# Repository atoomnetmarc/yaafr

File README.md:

# What are this?

This is Yaafr, Yet Another AVR Fusebit Rescuer. It is large because of all the ZIF-sockets and does not even feature any mounting holes. It also has two IDC headers for expanding to programming clips or other adapters to rescue non-dip AVR microcontrollers.

It is be able to restore wrongly fused or locked AVR microcontrollers that support high voltage parallel (HVPP) programming or high voltage serial programming (HVSP).

This circuit has been inspired by these projects:

[RescueAVR](https://github.com/felias-fogg/RescueAVR) by Bernhard.\
[AVR Fuse Rescue Shield for Arduino Uno](https://github.com/4x1md/avr_frs_shield) by Dmitry Melnichansky.\
[Arduino-based AVR High Voltage Programmer](https://mightyohm.com/blog/2008/09/arduino-based-avr-high-voltage-programmer/) by Jeff Keyzer.\
[Atmega Fusebit Doctor](https://web.archive.org/web/20180225102717/http://mdiy.pl/atmega-fusebit-doctor-hvpp/?lang=en) by Paweł Kisielewski.

Firmware update 2.11 from the Atmega Fusebit Doctor for the atmega328p has been tested and is working. The [original site](https://files.elektroda.pl/437268,atmega-hvpp-fusebit-doctor_update11.html) does not exist anymore, but [SukkoPera](https://github.com/SukkoPera) has been so kind to archive the remains: https://github.com/SukkoPera/avr-fusebit-doctor/

Firmware from RescueAVR in FBD_MODE works also, but may not contain support for all the chips (such as the AT90S1200).

# Status

This project is working for me, I can rescue all my locked AVRs. See below for what I have tested and validated to be working.

While the schematic was carefully made, the PCB has not been fully tested yet.

I added the possibility to switch on and off AGND and AVCC because in many datasheets in one instance they must be connected and in the next they must not, however leaving the switches always on connected when it does not need to be then the rescues seem to work just fine.

# Checklists

## Functionality

| Thing                                         | Tested and working?       |
| --                                            | --                        |
| 40-pin DIP style A                            | :ballot_box_with_check:   |
| 40-pin DIP style B                            | :ballot_box_with_check:   |
| 28-pin DIP style A                            | :ballot_box_with_check:   |
| 20-pin DIP style A                            | :ballot_box_with_check:   |
| 20-pin DIP style B                            | :ballot_box_with_check:   |
| 14-pin DIP style A                            | :ballot_box_with_check:   |
| 8-pin DIP style A                             | :ballot_box_with_check:   |
| AVR Atmega fusebit doctor firmware 2.11       | :ballot_box_with_check:   |
| RescueAVR firmware                            | :ballot_box_with_check:   |
| Serial connection                             | :ballot_box_with_check:   |
| Fusebit doctor compatible expansion header    | :ballot_box_with_check:   |
| HVPP expansion header                         | :black_square_button:     |
| HVSP expansion header                         | :black_square_button:     |

## 40-pin DIP style A (AT90S8535)

| Model         | Signature         | Working                   |
| --            | --                | --                        |
| AT90S8535     | 0x1E 0x93 0x03    | :ballot_box_with_check:   |
| ATmega8535    | 0x1E 0x93 0x08    | :ballot_box_with_check:   |
| ATmega163     | 0x1E 0x94 0x02    | :ballot_box_with_check:   |
| ATmega323     | 0x1E 0x95 0x01    | :ballot_box_with_check:   |
| ATmega16A     | 0x1E 0x94 0x03    | :ballot_box_with_check:   |
| ATmega32A     | 0x1E 0x95 0x02    | :ballot_box_with_check:   |
| ATmega324A    | 0x1E 0x95 0x15    | :ballot_box_with_check:   |
| ATmega644PA   | 0x1E 0x96 0x0A    | :ballot_box_with_check:   |
| ATmega1284P   | 0x1E 0x97 0x05    | :ballot_box_with_check:   |

## 40-pin DIP style B (AT90S8515)

| Model         | Signature         | Working                   |
| --            | --                | --                        |
| AT90S4414     | 0x1E 0x92 0x01    | :ballot_box_with_check:   |
| AT90S8515     | 0x1E 0x93 0x01    | :ballot_box_with_check:   |
| ATmega8515    | 0x1E 0x93 0x06    | :ballot_box_with_check:   |
| ATmega161     | 0x1E 0x94 0x01    | :ballot_box_with_check:   |
| ATmega162     | 0x1E 0x94 0x04    | :ballot_box_with_check:   |

## 28-pin DIP style A (AT90S2333)

| Model     | Signature         | Working                   |
| --        | --                | --                        |
| AT90S2333 | 0x1E 0x91 0x05    | :ballot_box_with_check:   |
| AT90S4433 | 0x1E 0x92 0x03    | :ballot_box_with_check:   |
| ATmega8   | 0x1E 0x93 0x07    | :ballot_box_with_check:   |
| ATmega48  | 0x1E 0x92 0x05    | :ballot_box_with_check:   |
| ATmega88  | 0x1E 0x93 0x0A    | :ballot_box_with_check:   |
| ATmega168 | 0x1E 0x94 0x06    | :ballot_box_with_check:   |
| ATmega328 | 0x1E 0x95 0x14    | :ballot_box_with_check:   |
| ATtiny48  | 0x1E 0x92 0x09    | :ballot_box_with_check:   |
| ATtiny88  | 0x1E 0x93 0x11    | :ballot_box_with_check:   |

Adapter for TQFP32: https://github.com/atoomnetmarc/Fusebit-Doctor-TQFP32-adapter

## 20-pin DIP style A (AT90S1200)

| Model         | Signature         | Working                   |
| --            | --                | --                        |
| AT90S1200     | 0x1E 0x90 0x01    | :ballot_box_with_check:   |
| AT90S2313     | 0x1E 0x91 0x01    | :ballot_box_with_check:   |
| ATtiny2313    | 0x1E 0x91 0x0A    | :ballot_box_with_check:   |
| ATtiny2313A   | 0x1E 0x91 0x0A    | :ballot_box_with_check:   |
| ATtiny4313    | 0x1E 0x92 0x0D    | :ballot_box_with_check:   |

## 20-pin DIP style B (ATtiny26)

| Model         | Signature         | Working                   |
| --            | --                | --                        |
| ATtiny26      | 0x1E 0x91 0x09    | :ballot_box_with_check:   |
| ATtiny261A    | 0x1E 0x91 0x0C    | :ballot_box_with_check:   |
| ATtiny461     | 0x1E 0x92 0x08    | :ballot_box_with_check:   |
| ATtiny461A    | 0x1E 0x92 0x08    | :ballot_box_with_check:   |
| ATtiny861A    | 0x1E 0x93 0x0D    | :ballot_box_with_check:   |

## 14-pin DIP style A (ATtiny24)

| Model     | Signature         | Working                   |
| --        | --                | --                        |
| ATtiny24  | 0x1E 0x91 0x0B    | :ballot_box_with_check:   |

## 8-pin DIP style A (AT90S2323)

| Model     | Signature         | Working                   |
| --        | --                | --                        |
| AT90S2323 | 0x1E 0x91 0x02    | :ballot_box_with_check:   |
| AT90S2343 | 0x1E 0x91 0x03    | :ballot_box_with_check:   |
| ATtiny12  | 0x1E 0x90 0x05    | :ballot_box_with_check:   |
| ATtiny15  | 0x1E 0x90 0x06    | :ballot_box_with_check:   |
| ATtiny13  | 0x1E 0x90 0x07    | :ballot_box_with_check:   |
| ATtiny25  | 0x1E 0x91 0x08    | :ballot_box_with_check:   |
| ATtiny45  | 0x1E 0x92 0x06    | :ballot_box_with_check:   |
| ATtiny85  | 0x1E 0x93 0x0B    | :ballot_box_with_check:   |

# Errata

## PCB V1.1

- No known erratum, however this pcb version has not been made yet.

## PCB V1.0

- 10.16mm wide 28-pin ZIF socket X3 seems to be unobtanium. Changed for 7.62mm wide 'narrow' 28-pin zif socket in V1.1 pcb.

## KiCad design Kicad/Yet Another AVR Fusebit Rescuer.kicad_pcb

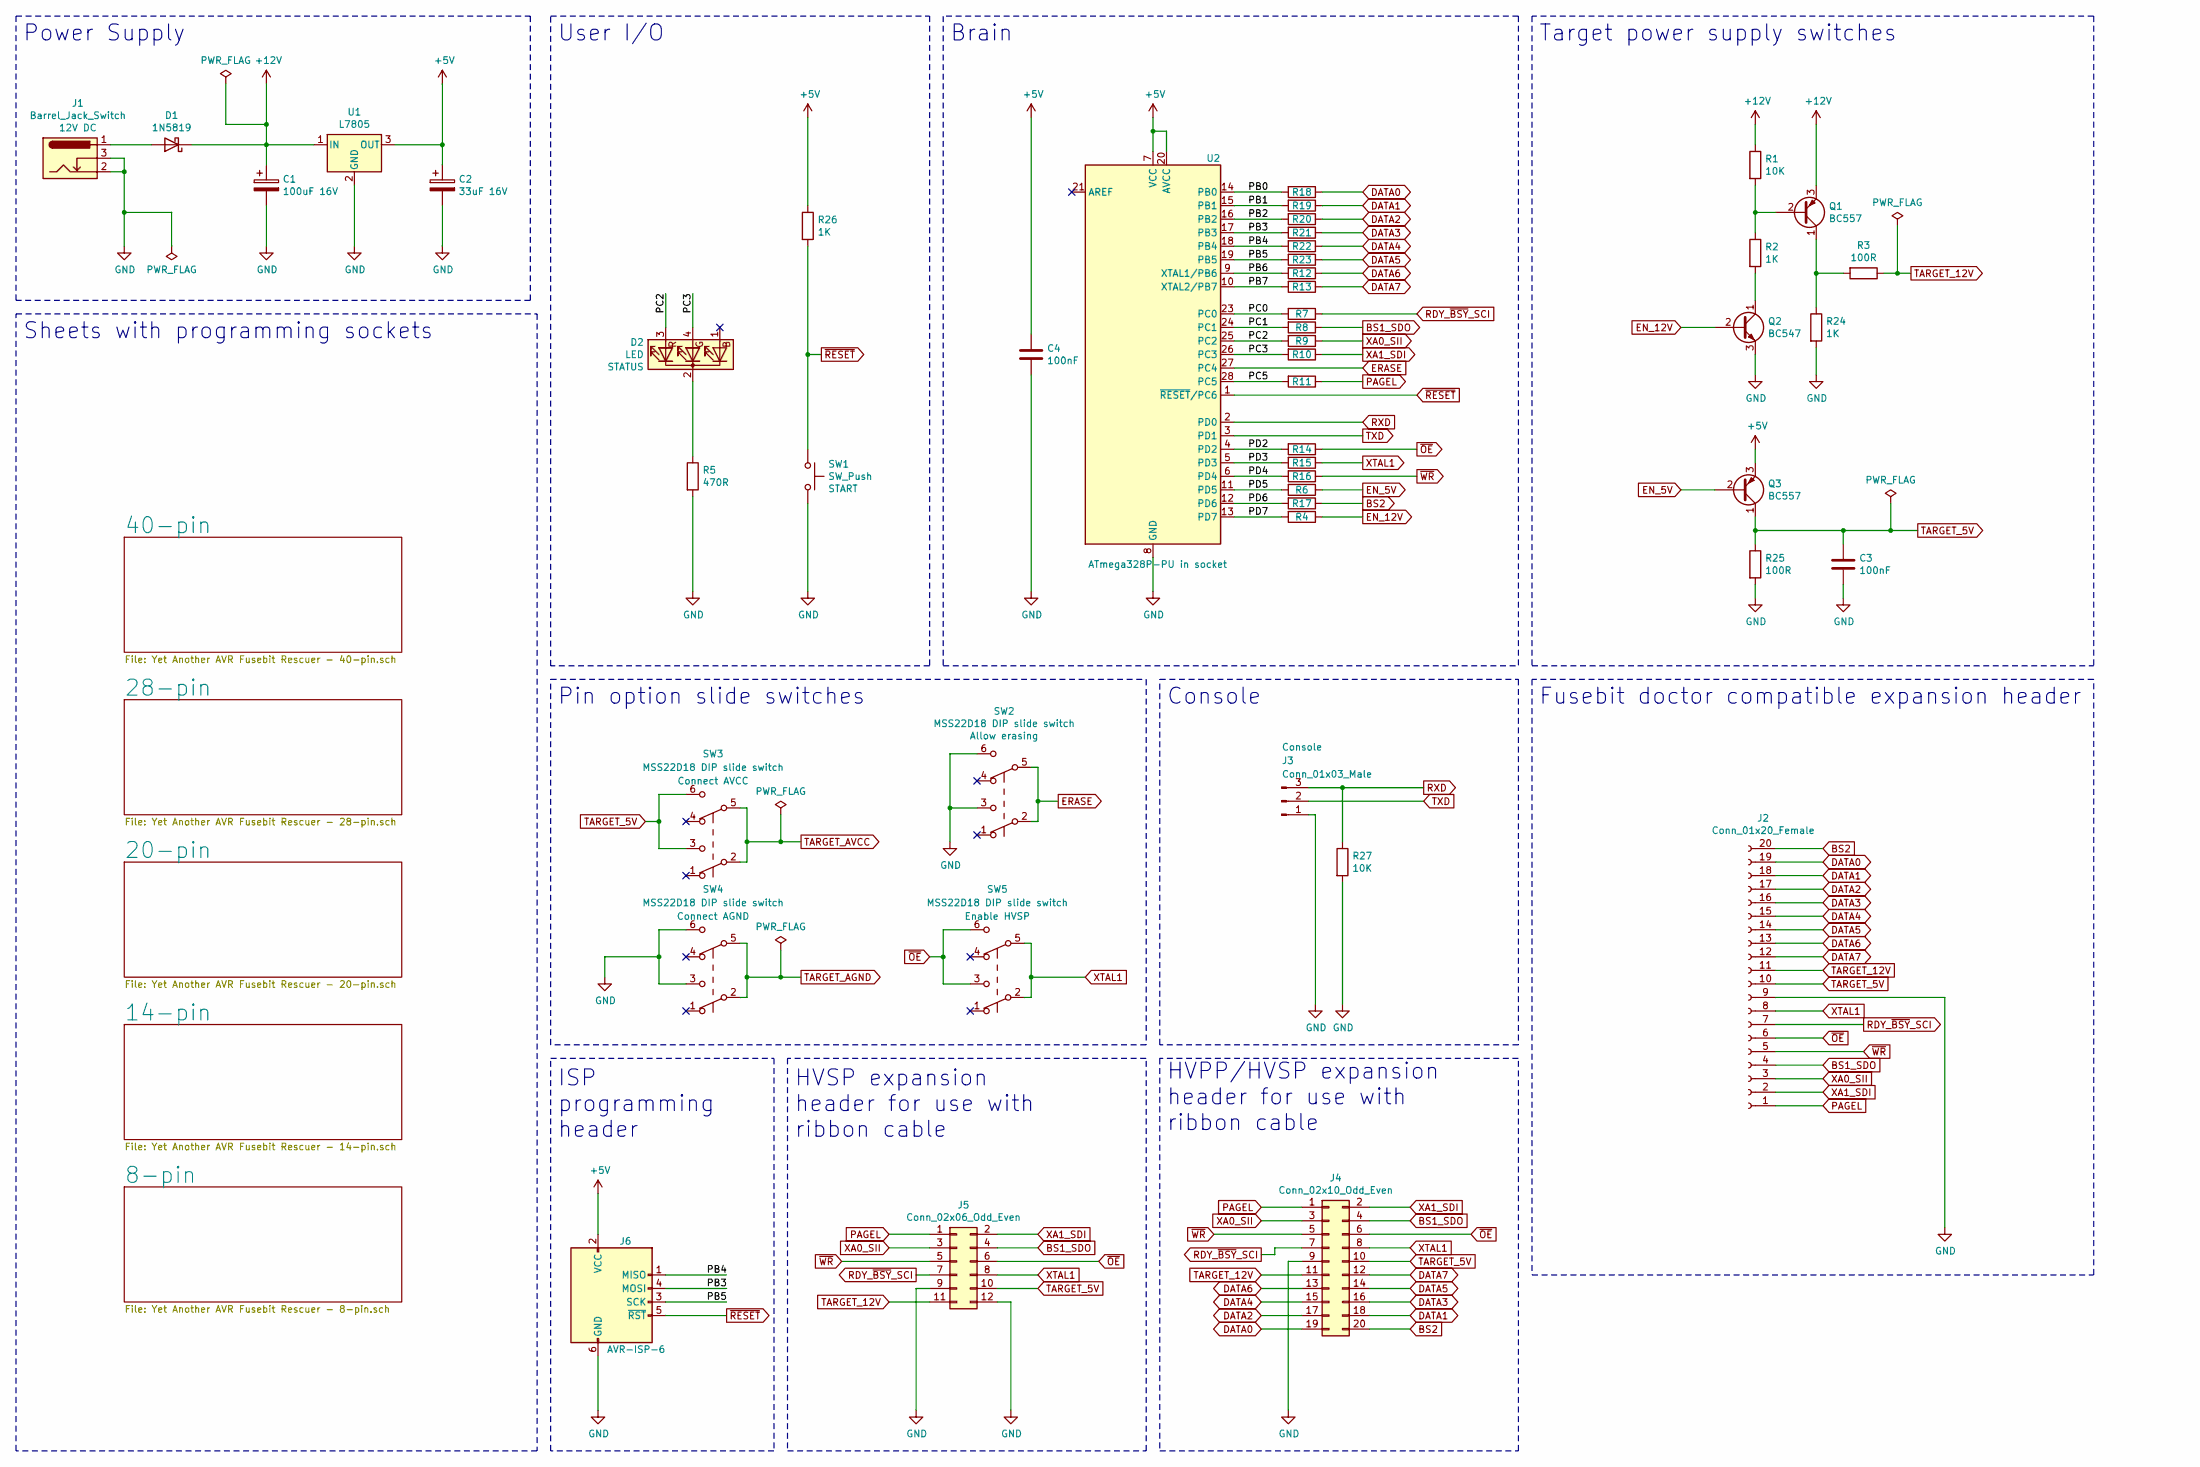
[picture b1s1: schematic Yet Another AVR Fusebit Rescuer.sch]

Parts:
C1: 100uF 16V; CP_Radial_D6.3mm_P2.50mm
C2: 33uF 16V; CP_Radial_D6.3mm_P2.50mm
C3, C4: 100nF; C_Disc_D5.1mm_W3.2mm_P5.00mm
D1: 1N5819; D_DO-15_P12.70mm_Horizontal
D2: LED; LED_D5.0mm-4_RGB
J1: Barrel_Jack_Switch; BarrelJack_Horizontal
J2: Conn_01x20_Female; PinSocket_1x20_P2.54mm_Vertical
J3: Conn_01x03_Male; PinHeader_1x03_P2.54mm_Horizontal
J4: Conn_02x10_Odd_Even; IDC-Header_2x10_P2.54mm_Vertical
J5: Conn_02x06_Odd_Even; IDC-Header_2x06_P2.54mm_Vertical
J6: AVR-ISP-6; IDC-Header_2x03_P2.54mm_Vertical
Q1, Q3: BC557; TO-92_Wide
Q2: BC547; TO-92_Wide
R1, R27: 10K; R_Axial_DIN0207_L6.3mm_D2.5mm_P10.16mm_Horizontal
R2, R4, R6, R7, R8, R9, R10, R11, R12, R13, R14, R15, R16, R17, R18, R19, R20, R21, R22, R23, R24, R26: 1K; R_Axial_DIN0207_L6.3mm_D2.5mm_P10.16mm_Horizontal
R3, R25: 100R; R_Axial_DIN0207_L6.3mm_D2.5mm_P10.16mm_Horizontal
R5: 470R; R_Axial_DIN0207_L6.3mm_D2.5mm_P10.16mm_Horizontal
SW1: SW_Push; SW_PUSH_6mm
SW2, SW3, SW4, SW5: MSS22D18 DIP slide switch; SW_CuK_JS202011CQN_DPDT_Straight
U1: L7805; TO-220-3_Horizontal_TabDown
U2: ATmega328P-PU in socket; DIP-28_W7.62mm

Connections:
+5V: C2.1, C4.1, J6.2 (VCC), Q3.3 (E), R26.1, U1.3 (OUT), U2.7 (VCC), U2.20 (AVCC)
+12V: C1.1, D1.1 (K), Q1.3 (E), R1.1, U1.1 (IN)
/PB0: R18.2, U2.14 (PB0)
/PB1: R19.2, U2.15 (PB1)
/PB2: R20.2, U2.16 (PB2)
/PB3: J6.4 (MOSI), R21.2, U2.17 (PB3)
/PB4: J6.1 (MISO), R22.2, U2.18 (PB4)
/PB5: J6.3 (SCK), R23.2, U2.19 (PB5)
/PB6: R12.2, U2.9 (XTAL1/PB6)
/PB7: R13.2, U2.10 (XTAL2/PB7)
/PC0: R7.2, U2.23 (PC0)
/PC1: R8.2, U2.24 (PC1)
/PC2: D2.3 (RA), R9.2, U2.25 (PC2)
/PC3: D2.4 (GA), R10.2, U2.26 (PC3)
/PC5: R11.2, U2.28 (PC5)
/PD2: R14.2, U2.4 (PD2)
/PD3: R15.2, U2.5 (PD3)
/PD4: R16.2, U2.6 (PD4)
/PD5: R6.2, U2.11 (PD5)
/PD6: R17.2, U2.12 (PD6)
/PD7: R4.2, U2.13 (PD7)
BS1_SDO: J2.4, J4.4, J5.4, R8.1; also elsewhere on the board
BS2: J2.20, J4.20, R17.1; also elsewhere on the board
DATA0: J2.19, J4.19, R18.1; also elsewhere on the board
DATA1: J2.18, J4.18, R19.1; also elsewhere on the board
DATA2: J2.17, J4.17, R20.1; also elsewhere on the board
DATA3: J2.16, J4.16, R21.1; also elsewhere on the board
DATA4: J2.15, J4.15, R22.1; also elsewhere on the board
DATA5: J2.14, J4.14, R23.1; also elsewhere on the board
DATA6: J2.13, J4.13, R12.1; also elsewhere on the board
DATA7: J2.12, J4.12, R13.1; also elsewhere on the board
EN_5V: Q3.2 (B), R6.1
EN_12V: Q2.2 (B), R4.1
ERASE: SW2.2 (B), SW2.5 (B), U2.27 (PC4)
GND: C1.2, C2.2, C3.2, C4.2, J1.2, J1.3, J2.9, J3.1, J4.9, J5.9, J5.12, J6.6 (GND), Q2.3 (E), R5.2, R24.2, R25.2, R27.2, SW1.2, SW2.3 (C), SW2.6 (C), SW4.3 (C), SW4.6 (C), U1.2 (GND), U2.8 (GND), U2.22 (GND); also elsewhere on the board
unnamed: D1.2 (A), J1.1
unnamed: D2.2 (K), R5.1
unnamed: Q1.1 (C), R3.2, R24.1
unnamed: Q1.2 (B), R1.2, R2.1
unnamed: Q2.1 (C), R2.2
PAGEL: J2.1, J4.1, J5.1, R11.1; also elsewhere on the board
RDY_~BSY~_SCI: J2.7, J4.7, J5.7, R7.1; also elsewhere on the board
RXD: J3.3, R27.1, U2.2 (PD0)
TARGET_5V: C3.1, J2.10, J4.10, J5.10, Q3.1 (C), R25.1, SW3.3 (C), SW3.6 (C); also elsewhere on the board
TARGET_12V: J2.11, J4.11, J5.11, R3.1; also elsewhere on the board
TARGET_AGND: SW4.2 (B), SW4.5 (B); also elsewhere on the board
TARGET_AVCC: SW3.2 (B), SW3.5 (B); also elsewhere on the board
TXD: J3.2, U2.3 (PD1)
XA0_SII: J2.3, J4.3, J5.3, R9.1; also elsewhere on the board
XA1_SDI: J2.2, J4.2, J5.2, R10.1; also elsewhere on the board
XTAL1: J2.8, J4.8, J5.8, R15.1, SW5.2 (B), SW5.5 (B); also elsewhere on the board
~OE: J2.6, J4.6, J5.6, R14.1, SW5.3 (C), SW5.6 (C); also elsewhere on the board
~RESET: J6.5 (~RST), R26.2, SW1.1, U2.1 (~RESET~/PC6)
~WR: J2.5, J4.5, J5.5, R16.1; also elsewhere on the board

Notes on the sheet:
Power Supply
Target power supply switches
Fusebit doctor compatible expansion header
User I/O
Console
Brain
Pin option slide switches
HVPP/HVSP expansion header for use with ribbon cable
HVSP expansion header for use with ribbon cable
ISP programming header
Sheets with programming sockets

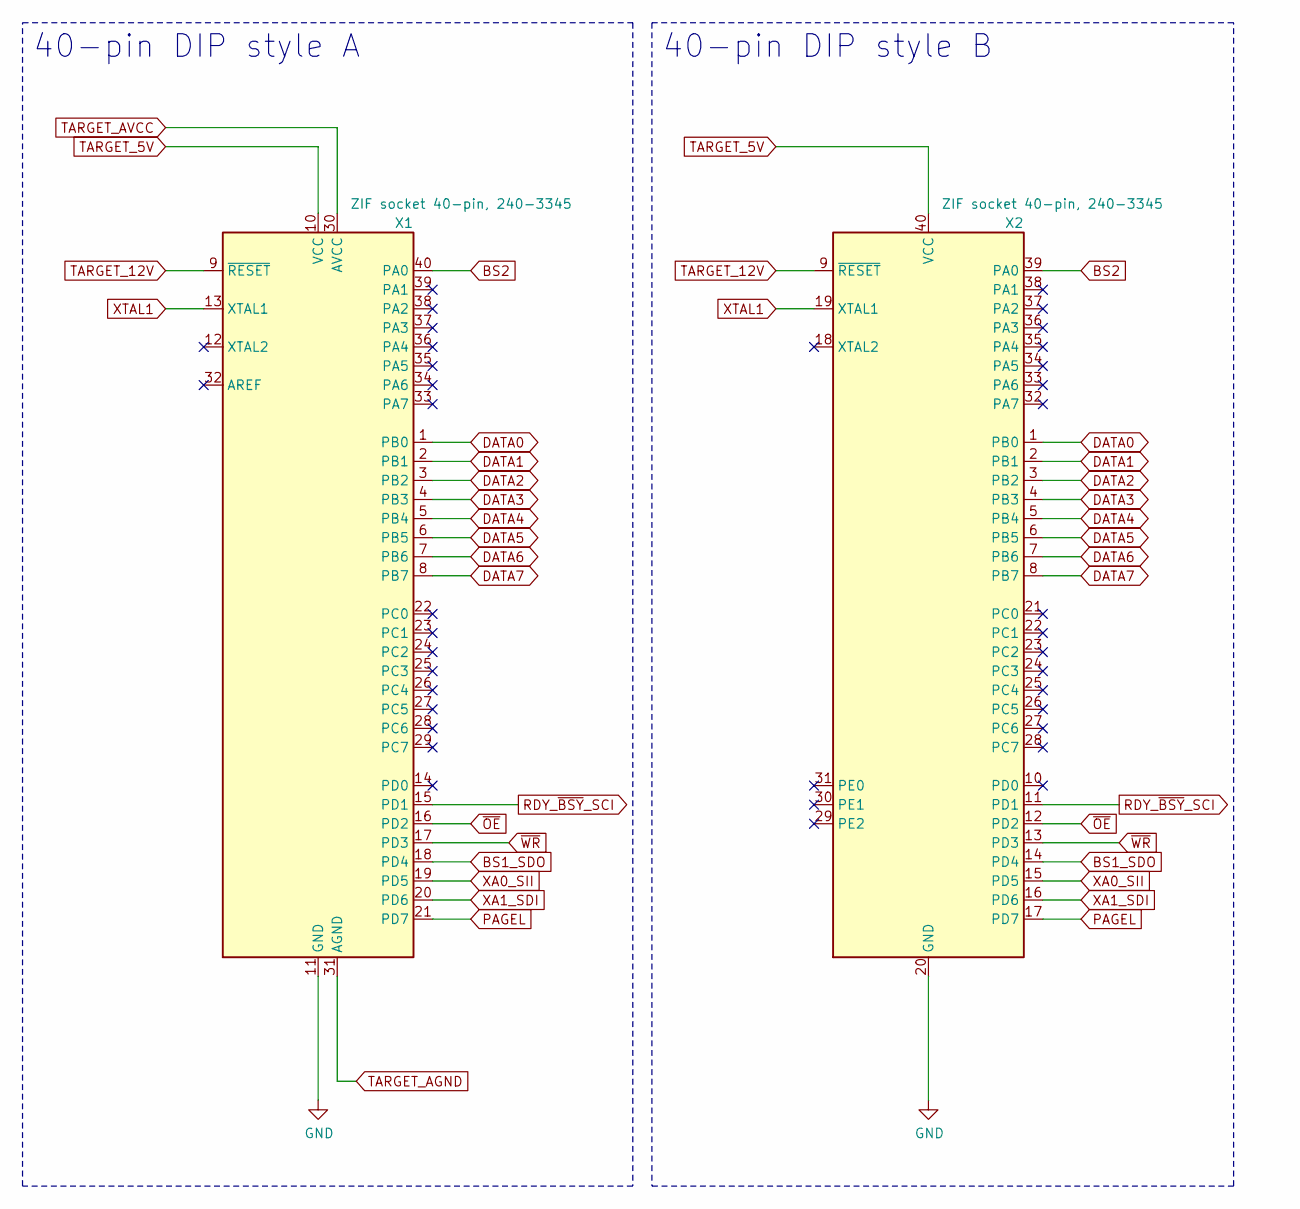
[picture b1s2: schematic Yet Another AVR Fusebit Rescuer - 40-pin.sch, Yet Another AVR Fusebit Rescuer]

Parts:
X1, X2: ZIF socket 40-pin, 240-3345; DIP_Socket-40_W11.9_W12.7_W15.24_W17.78_W18.5_3M_240-1280-0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

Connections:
BS1_SDO: X1.18 (PD4), X2.14 (PD4); also elsewhere on the board
BS2: X1.40 (PA0), X2.39 (PA0); also elsewhere on the board
DATA0: X1.1 (PB0), X2.1 (PB0); also elsewhere on the board
DATA1: X1.2 (PB1), X2.2 (PB1); also elsewhere on the board
DATA2: X1.3 (PB2), X2.3 (PB2); also elsewhere on the board
DATA3: X1.4 (PB3), X2.4 (PB3); also elsewhere on the board
DATA4: X1.5 (PB4), X2.5 (PB4); also elsewhere on the board
DATA5: X1.6 (PB5), X2.6 (PB5); also elsewhere on the board
DATA6: X1.7 (PB6), X2.7 (PB6); also elsewhere on the board
DATA7: X1.8 (PB7), X2.8 (PB7); also elsewhere on the board
GND: X1.11 (GND), X2.20 (GND); also elsewhere on the board
PAGEL: X1.21 (PD7), X2.17 (PD7); also elsewhere on the board
RDY_~BSY~_SCI: X1.15 (PD1), X2.11 (PD1); also elsewhere on the board
TARGET_5V: X1.10 (VCC), X2.40 (VCC); also elsewhere on the board
TARGET_12V: X1.9 (~RESET), X2.9 (~RESET); also elsewhere on the board
TARGET_AGND: X1.31 (AGND); also elsewhere on the board
TARGET_AVCC: X1.30 (AVCC); also elsewhere on the board
XA0_SII: X1.19 (PD5), X2.15 (PD5); also elsewhere on the board
XA1_SDI: X1.20 (PD6), X2.16 (PD6); also elsewhere on the board
XTAL1: X1.13 (XTAL1), X2.19 (XTAL1); also elsewhere on the board
~OE: X1.16 (PD2), X2.12 (PD2); also elsewhere on the board
~WR: X1.17 (PD3), X2.13 (PD3); also elsewhere on the board

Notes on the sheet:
40-pin DIP style A
40-pin DIP style B

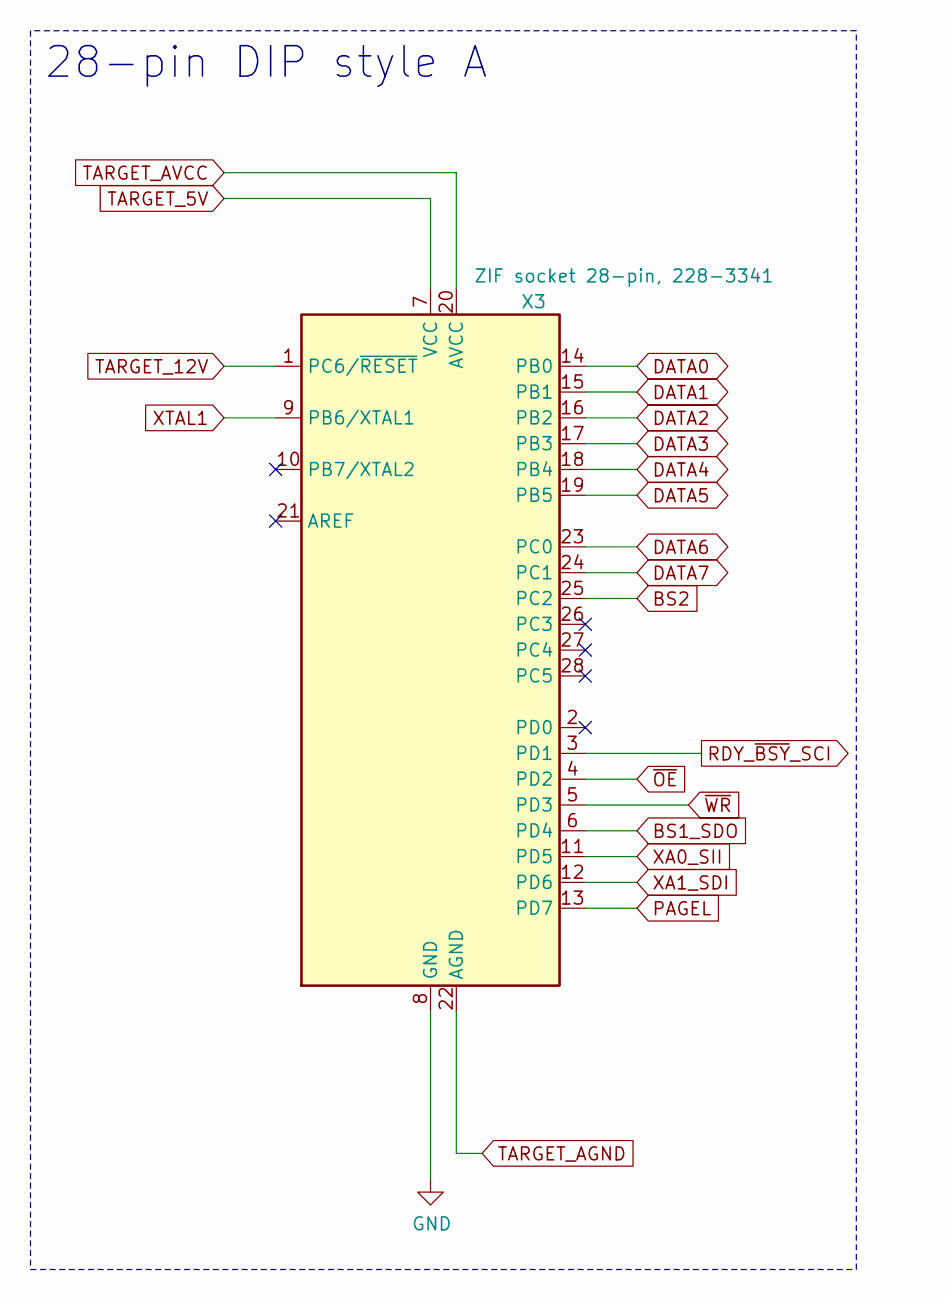
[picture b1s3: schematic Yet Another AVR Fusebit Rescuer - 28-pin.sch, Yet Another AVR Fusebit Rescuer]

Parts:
X3: ZIF socket 28-pin, 228-3341; DIP_Socket-28_228-3341

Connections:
BS1_SDO: X3.6 (PD4); also elsewhere on the board
BS2: X3.25 (PC2); also elsewhere on the board
DATA0: X3.14 (PB0); also elsewhere on the board
DATA1: X3.15 (PB1); also elsewhere on the board
DATA2: X3.16 (PB2); also elsewhere on the board
DATA3: X3.17 (PB3); also elsewhere on the board
DATA4: X3.18 (PB4); also elsewhere on the board
DATA5: X3.19 (PB5); also elsewhere on the board
DATA6: X3.23 (PC0); also elsewhere on the board
DATA7: X3.24 (PC1); also elsewhere on the board
GND: X3.8 (GND); also elsewhere on the board
PAGEL: X3.13 (PD7); also elsewhere on the board
RDY_~BSY~_SCI: X3.3 (PD1); also elsewhere on the board
TARGET_5V: X3.7 (VCC); also elsewhere on the board
TARGET_12V: X3.1 (PC6/~RESET); also elsewhere on the board
TARGET_AGND: X3.22 (AGND); also elsewhere on the board
TARGET_AVCC: X3.20 (AVCC); also elsewhere on the board
XA0_SII: X3.11 (PD5); also elsewhere on the board
XA1_SDI: X3.12 (PD6); also elsewhere on the board
XTAL1: X3.9 (PB6/XTAL1); also elsewhere on the board
~OE: X3.4 (PD2); also elsewhere on the board
~WR: X3.5 (PD3); also elsewhere on the board

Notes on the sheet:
28-pin DIP style A

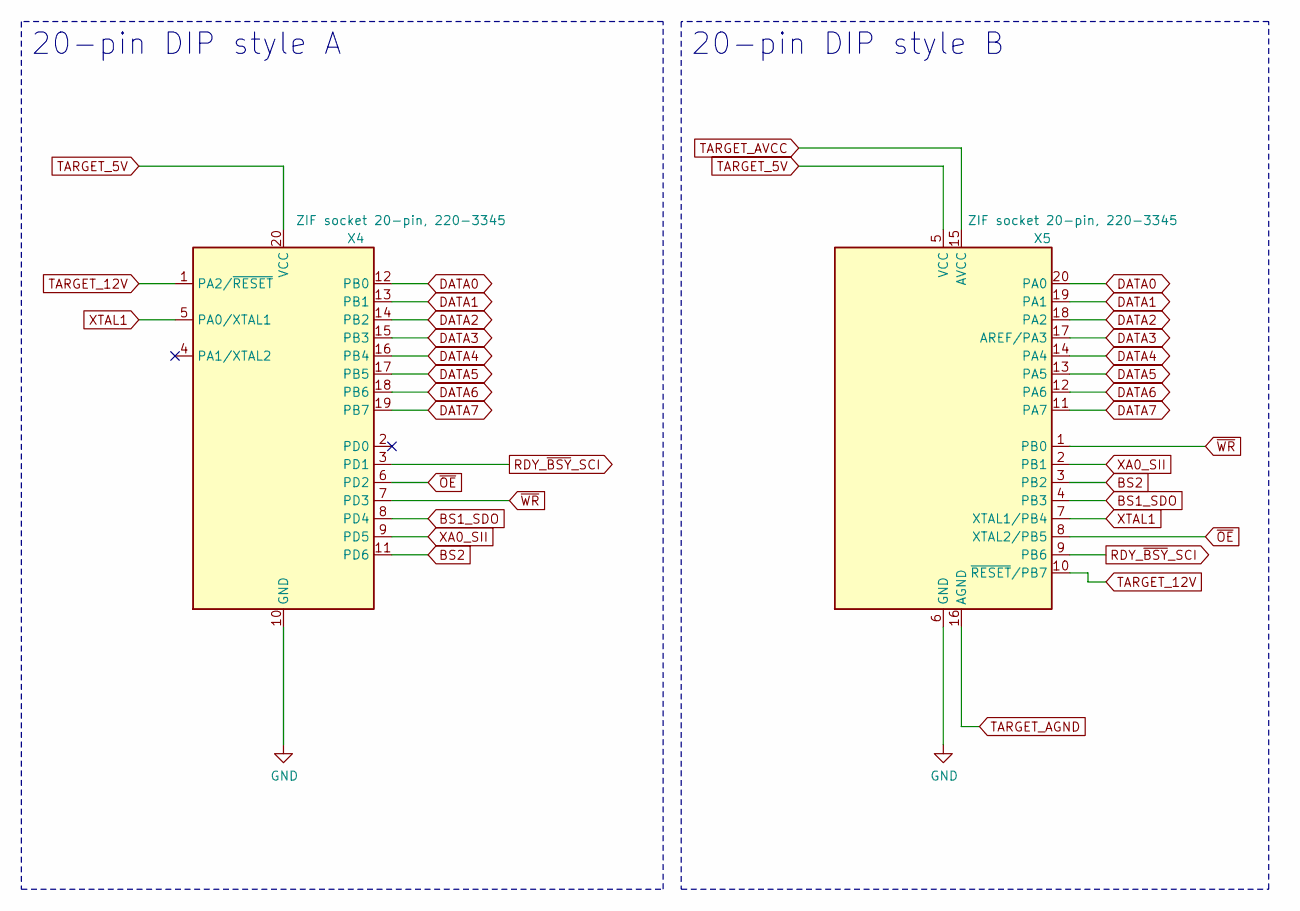
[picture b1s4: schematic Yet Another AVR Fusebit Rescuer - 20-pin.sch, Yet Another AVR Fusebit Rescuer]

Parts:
X4, X5: ZIF socket 20-pin, 220-3345; DIP_Socket-20_W4.3_W5.08_W7.62_W10.16_W10.9_3M_220-3342-00-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

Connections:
BS1_SDO: X4.8 (PD4), X5.4 (PB3); also elsewhere on the board
BS2: X4.11 (PD6), X5.3 (PB2); also elsewhere on the board
DATA0: X4.12 (PB0), X5.20 (PA0); also elsewhere on the board
DATA1: X4.13 (PB1), X5.19 (PA1); also elsewhere on the board
DATA2: X4.14 (PB2), X5.18 (PA2); also elsewhere on the board
DATA3: X4.15 (PB3), X5.17 (AREF/PA3); also elsewhere on the board
DATA4: X4.16 (PB4), X5.14 (PA4); also elsewhere on the board
DATA5: X4.17 (PB5), X5.13 (PA5); also elsewhere on the board
DATA6: X4.18 (PB6), X5.12 (PA6); also elsewhere on the board
DATA7: X4.19 (PB7), X5.11 (PA7); also elsewhere on the board
GND: X4.10 (GND), X5.6 (GND); also elsewhere on the board
RDY_~BSY~_SCI: X4.3 (PD1), X5.9 (PB6); also elsewhere on the board
TARGET_5V: X4.20 (VCC), X5.5 (VCC); also elsewhere on the board
TARGET_12V: X4.1 (PA2/~RESET), X5.10 (~RESET~/PB7); also elsewhere on the board
TARGET_AGND: X5.16 (AGND); also elsewhere on the board
TARGET_AVCC: X5.15 (AVCC); also elsewhere on the board
XA0_SII: X4.9 (PD5), X5.2 (PB1); also elsewhere on the board
XTAL1: X4.5 (PA0/XTAL1), X5.7 (XTAL1/PB4); also elsewhere on the board
~OE: X4.6 (PD2), X5.8 (XTAL2/PB5); also elsewhere on the board
~WR: X4.7 (PD3), X5.1 (PB0); also elsewhere on the board

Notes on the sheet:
20-pin DIP style A
20-pin DIP style B

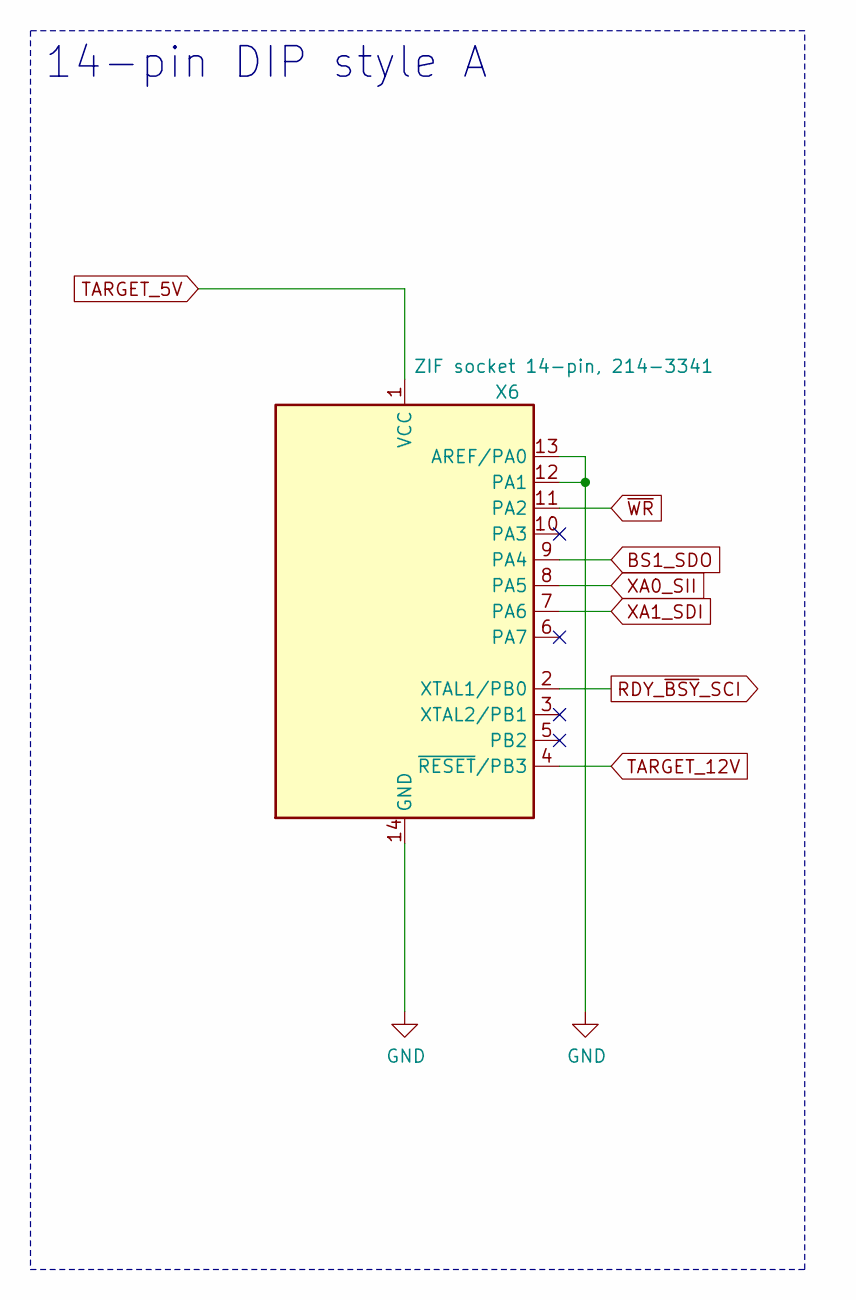
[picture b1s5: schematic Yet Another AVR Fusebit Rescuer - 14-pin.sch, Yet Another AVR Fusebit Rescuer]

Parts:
X6: ZIF socket 14-pin, 214-3341; DIP_Socket-14_W4.3_W5.08_W7.62_W10.16_W10.9_3M_214-3339-00-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

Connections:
BS1_SDO: X6.9 (PA4); also elsewhere on the board
GND: X6.12 (PA1), X6.13 (AREF/PA0), X6.14 (GND); also elsewhere on the board
RDY_~BSY~_SCI: X6.2 (XTAL1/PB0); also elsewhere on the board
TARGET_5V: X6.1 (VCC); also elsewhere on the board
TARGET_12V: X6.4 (~RESET~/PB3); also elsewhere on the board
XA0_SII: X6.8 (PA5); also elsewhere on the board
XA1_SDI: X6.7 (PA6); also elsewhere on the board
~WR: X6.11 (PA2); also elsewhere on the board

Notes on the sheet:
14-pin DIP style A

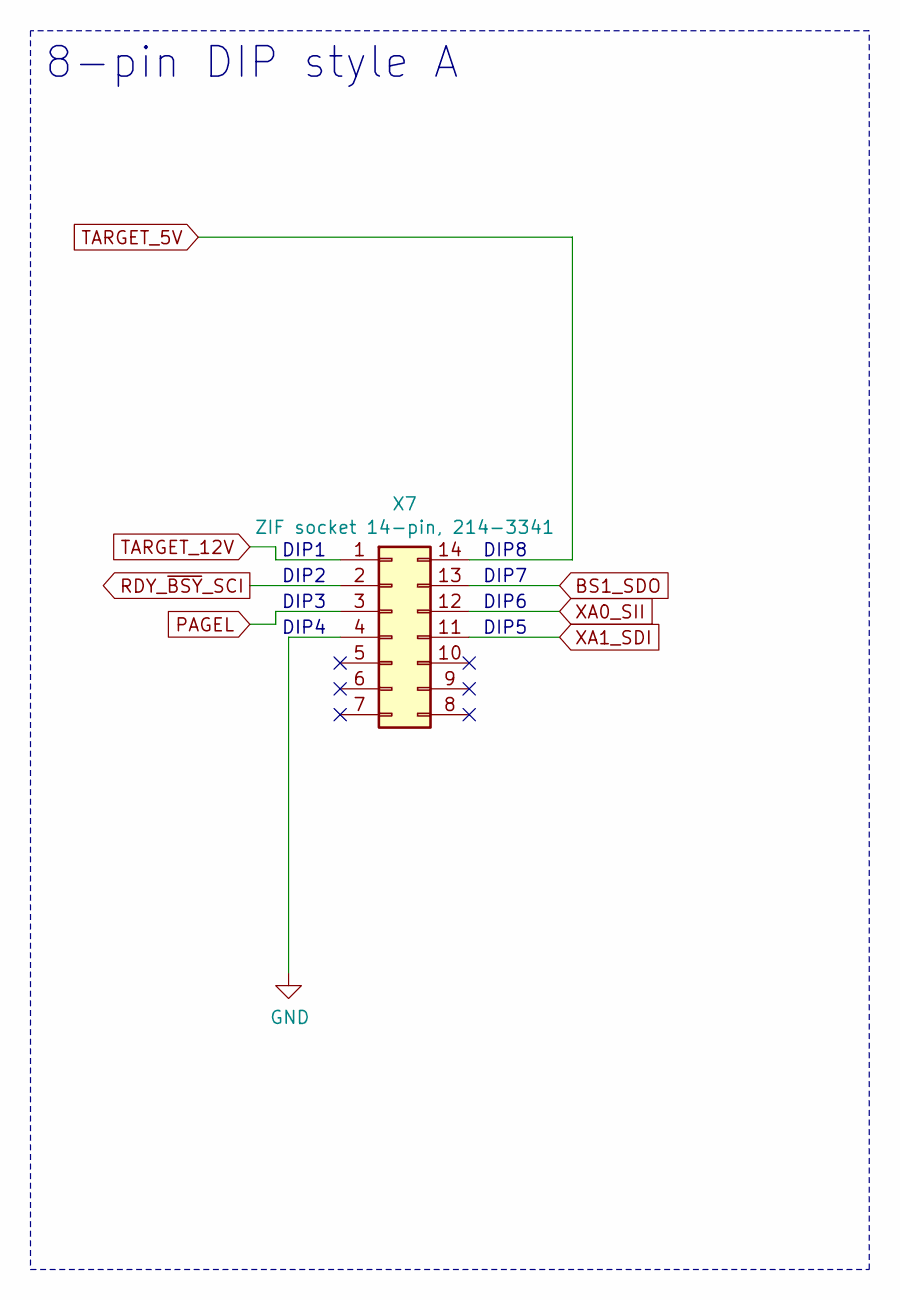
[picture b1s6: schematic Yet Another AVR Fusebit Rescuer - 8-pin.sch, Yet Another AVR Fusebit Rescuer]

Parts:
X7: ZIF socket 14-pin, 214-3341; DIP_Socket-14_W4.3_W5.08_W7.62_W10.16_W10.9_3M_214-3339-00-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

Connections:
BS1_SDO: X7.13; also elsewhere on the board
GND: X7.4; also elsewhere on the board
PAGEL: X7.3; also elsewhere on the board
RDY_~BSY~_SCI: X7.2; also elsewhere on the board
TARGET_5V: X7.14; also elsewhere on the board
TARGET_12V: X7.1; also elsewhere on the board
XA0_SII: X7.12; also elsewhere on the board
XA1_SDI: X7.11; also elsewhere on the board

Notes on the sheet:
8-pin DIP style A
DIP5
DIP6
DIP7
DIP8
DIP1
DIP2
DIP3
DIP4

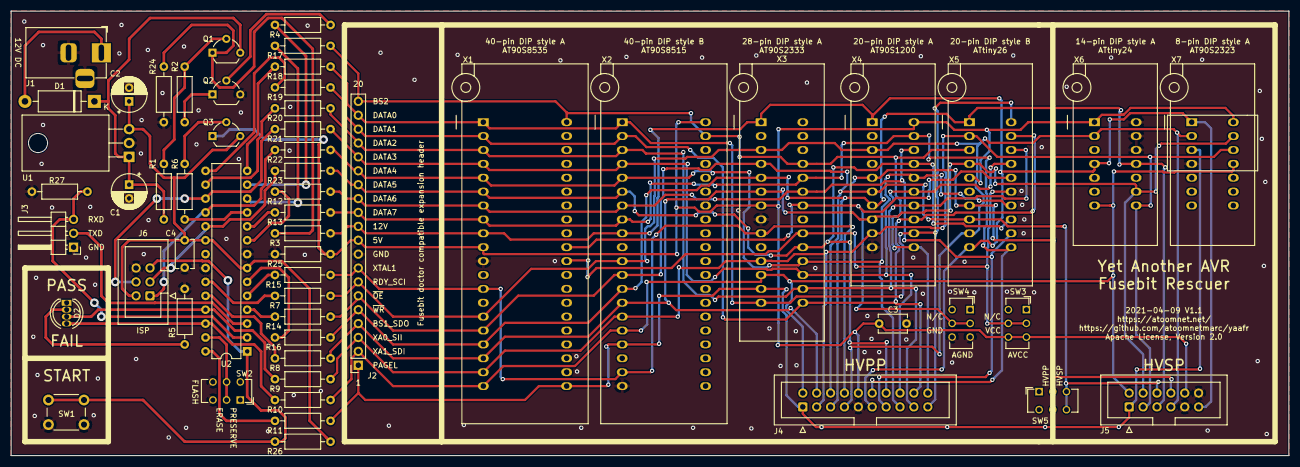
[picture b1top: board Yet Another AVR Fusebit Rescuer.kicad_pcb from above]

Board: 2 copper layers, 233.7 x 81.3 mm, 56 parts (0 on the bottom side), 54 nets.

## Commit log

2021-09-22 Test more ATtiny style B.
2021-09-25 Minor changes.
2021-10-09 Test ATtiny88.
2023-03-06 Updated dead link to Atmega Fusebit Doctor.
2024-02-08 AT90S2333 tested and works.
2024-02-08 Fusebit doctor compatible expansion header tested and working.

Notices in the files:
Kicad/Yet Another AVR Fusebit Rescuer.kicad_pcb:
Apache License, Version 2.0
README.md:
License: Apache 2.0
